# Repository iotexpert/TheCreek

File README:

-----------
creekServer
-----------
jsp that displays the output of the creek database

to build it use 'ant compile' or 'ant'
to deploy it type 'and install'
the username and password is hardcoded in the build file

-------------
creekFirmware
-------------
a zip file of the firmware running on the psoc

----------
getCreek
---------
The program that runs on the rasperry PI.
reads the i2c
figures out what the adc value means
writes the data into the database on the RPI

to build
ant build

to install - (which basically copies the directory into the right place
ant install 

To make the program run on the RPI you need to have 
crontab -l
* * * * * /home/pi/getCreek/printData

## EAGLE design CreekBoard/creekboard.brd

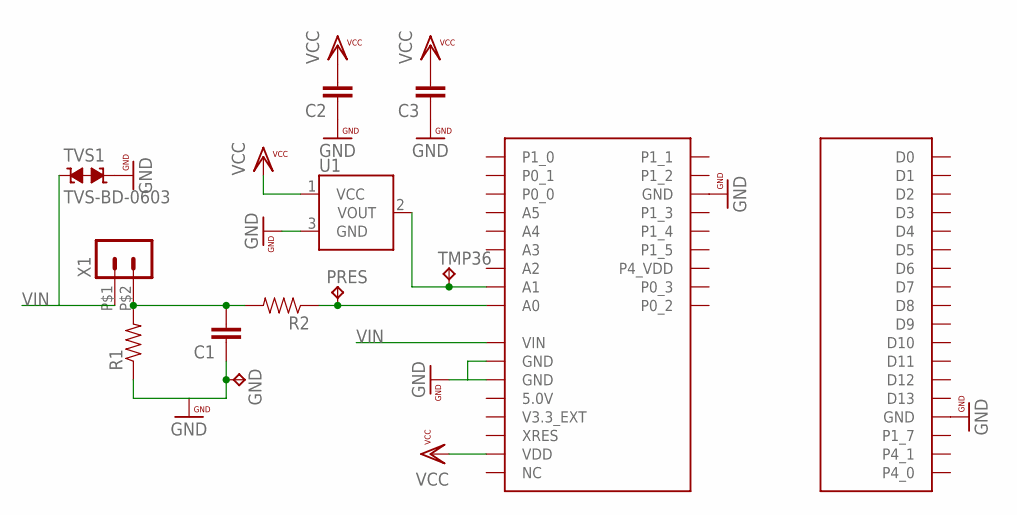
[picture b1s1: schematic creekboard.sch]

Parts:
C1, C2, C3: CAP0603-CAP; 0603-CAP
GND: TP-040
PRES: TP-040
R1: RESISTOR0805-RES; 0805
R2: RESISTOR0603-RES; 0603-RES
TMP36: TP-040
TVS1: TVS-BD-0603; TVS0603
U1: TMP36GT9; TO-92
U2: PIONEERNO_SILK; PIONEER
X1: HEADER_POS2_43650-0200; 43650-0200

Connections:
GND: C1.1, C2.1, C3.1, GND.1, R1.1, TVS1.2, U1.3 (GND), U2.GND@2 (GND), U2.GND@3 (GND), U2.GND@3R (GND), U2.GND@7 (GND)
unnamed: C1.2, R1.2, R2.2, X1.P$2 (2)
unnamed: PRES.1, R2.1, U2.A0
unnamed: TMP36.1, U1.2 (VOUT), U2.A1
VCC: C2.2, C3.2, U1.1 (VCC), U2.P4_VDD1 (VDD)
VIN: TVS1.1, U2.VIN, X1.P$1 (1)

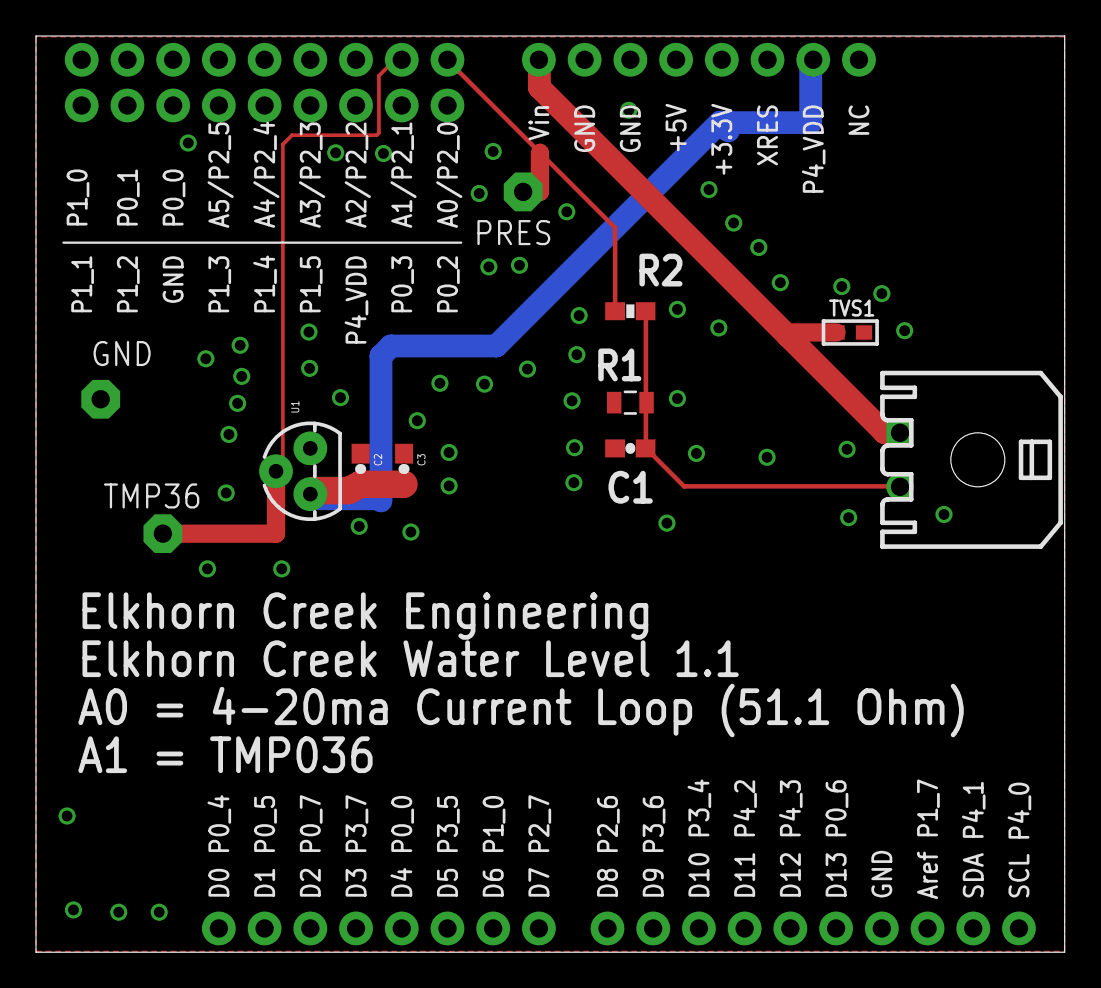
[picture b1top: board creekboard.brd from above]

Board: 2 copper layers, 57.1 x 50.9 mm, 12 parts (0 on the bottom side), 6 nets.

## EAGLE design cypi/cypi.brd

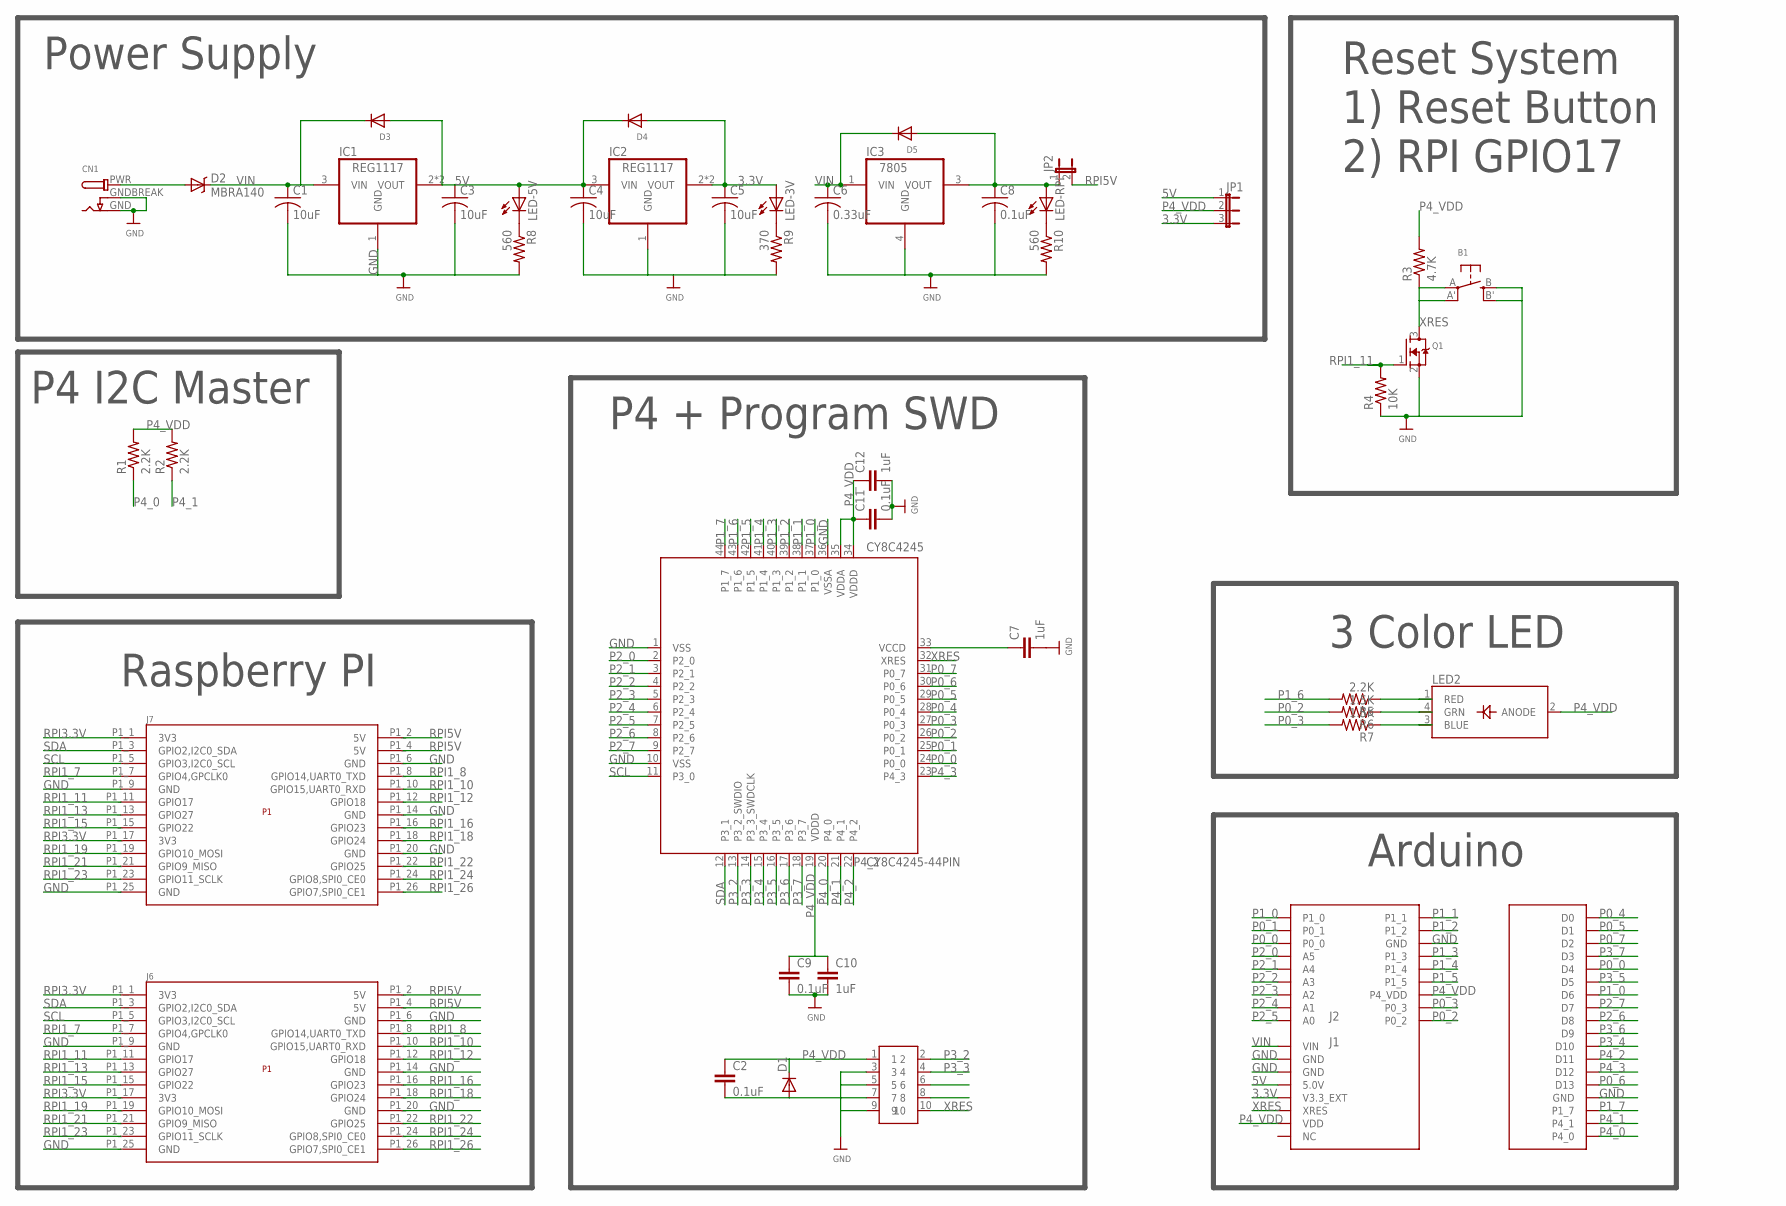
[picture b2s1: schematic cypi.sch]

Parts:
B1: SWITCH_TACT_SMT; EVQ-Q2
C1, C3, C4, C5: 10uF; C0805
C2, C9, C11: 0.1uF; 1206
C6: 0.33uF; C0805
C7, C10, C12: 1uF; 1206
C8: 0.1uF; C0805
CN1: DCBARRELPTH; DCJACK_2MM_PTH
CY8C4245: CY8C4245-44PIN; TQFP-10X10-44
D1: DIODEHV; DIODE-HV
D2: MBRA140; SMA-DIODE
D3, D4, D5: DIODESOD-123; SOD-123
IC1: REG1117; SOT223
IC2: REG1117; SOT223; MPN REG1117
IC3: 7805; DPAK
J5: SAMTEC; FTSH-105-01-XXX-DV-K
J6: RASPBERRY-PI_REV2PINONLY; RPI-PINS
J7: RASPBERRY-PI_REV2
JP1: JP2E; JP2
JP2: JUMPER-2PTH; 1X02
LED2: LED_RGB_PLCC4; RGBLED_PLCC4
LED-3V, LED-5V: LEDCHIPLED_0805; CHIPLED_0805
LED-RPI: LEDCHIPLED_0805; CHIPLED_0805
Q1: MOSFET-NREFLOW; SOT23-R
R1, R2, R5: 2.2K; 0805
R3: 4.7K; 0805
R4: 10K; 0805
R6, R7: 1.5K; 0805
R8, R10: 560; 0805
R9: 370; 0805
U1: PIONEERNO_SILK; PIONEER

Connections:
3.3V: C5.1, D4.A, IC2.2 (VOUT), IC2.4 (VOUT), JP1.3, LED-3V.A, U1.3.3V (V3.3_EXT)
5V: C3.1, C4.1, D3.A, D4.C, IC1.2 (VOUT), IC1.4 (VOUT), IC2.3 (VIN), JP1.1, LED-5V.A, U1.5V (5.0V)
GND: B1.B (S), B1.B' (S1), C1.2, C2.2, C3.2, C4.2, C5.2, C6.2, C7.2, C8.2, C9.2, C10.2, C11.2, C12.2, CN1.GND, CN1.GNDBREAK, CY8C4245.1 (VSS), CY8C4245.10 (VSS), CY8C4245.36 (VSSA), D1.A, IC1.1 (GND), IC2.1 (GND), IC3.4 (GND), J5.3, J5.5, J5.7, J5.9, J6.P1_6 (GND), J6.P1_9 (GND), J6.P1_14 (GND), J6.P1_20 (GND), J6.P1_25 (GND), J7.P1_6 (GND), J7.P1_9 (GND), J7.P1_14 (GND), J7.P1_20 (GND), J7.P1_25 (GND), Q1.2 (S), R4.1, R8.2, R9.2, R10.2, U1.GND@2 (GND), U1.GND@3 (GND), U1.GND@3R (GND), U1.GND@7 (GND)
unnamed: C7.1, CY8C4245.33 (VCCD)
unnamed: C8.1, D5.A, IC3.3 (VOUT), JP2.1, LED-RPI.A
unnamed: CN1.PWR, D2.A
unnamed: LED2.1 (RED), R5.1
unnamed: LED2.4 (GRN), R6.1
unnamed: LED2.3 (BLUE), R7.1
unnamed: LED-5V.C, R8.1
unnamed: LED-3V.C, R9.1
unnamed: LED-RPI.C, R10.1
P0_0: CY8C4245.24 (P0_0), U1.D4, U1.P0_0
P0_1: CY8C4245.25 (P0_1), U1.P0_1
P0_2: CY8C4245.26 (P0_2), R6.2, U1.P0_2
P0_3: CY8C4245.27 (P0_3), R7.2, U1.P0_3
P0_4: CY8C4245.28 (P0_4), U1.D0
P0_5: CY8C4245.29 (P0_5), U1.D1
P0_6: CY8C4245.30 (P0_6), U1.D13
P0_7: CY8C4245.31 (P0_7), U1.D2
P1_0: CY8C4245.37 (P1_0), U1.D6, U1.P1_0
P1_1: CY8C4245.38 (P1_1), U1.P1_1
P1_2: CY8C4245.39 (P1_2), U1.P1_2
P1_3: CY8C4245.40 (P1_3), U1.P1_3
P1_4: CY8C4245.41 (P1_4), U1.P1_4
P1_5: CY8C4245.42 (P1_5), U1.P1_5
P1_6: CY8C4245.43 (P1_6), R5.2
P1_7: CY8C4245.44 (P1_7), U1.AREF (P1_7)
P2_0: CY8C4245.2 (P2_0), U1.A0 (A5)
P2_1: CY8C4245.3 (P2_1), U1.A1 (A4)
P2_2: CY8C4245.4 (P2_2), U1.A2 (A3)
P2_3: CY8C4245.5 (P2_3), U1.A3 (A2)
P2_4: CY8C4245.6 (P2_4), U1.A4 (A1)
P2_5: CY8C4245.7 (P2_5), U1.A5 (A0)
P2_6: CY8C4245.8 (P2_6), U1.D8
P2_7: CY8C4245.9 (P2_7), U1.D7
P3_2: CY8C4245.13 (P3_2_SWDIO), J5.2
P3_3: CY8C4245.14 (P3_3_SWDCLK), J5.4
P3_4: CY8C4245.15 (P3_4), U1.D10
P3_5: CY8C4245.16 (P3_5), U1.D5
P3_6: CY8C4245.17 (P3_6), U1.D9
P3_7: CY8C4245.18 (P3_7), U1.D3
P4_0: CY8C4245.20 (P4_0), R1.1, U1.SCL (P4_0)
P4_1: CY8C4245.21 (P4_1), R2.1, U1.SDA (P4_1)
P4_2: CY8C4245.22 (P4_2), U1.D11
P4_3: CY8C4245.23 (P4_3), U1.D12
P4_VDD: C2.1, C9.1, C10.1, C11.1, C12.1, CY8C4245.19 (VDDD), CY8C4245.34 (VDDD), CY8C4245.35 (VDDA), D1.C, J5.1, JP1.2, LED2.2 (ANODE), R1.2, R2.2, R3.2, U1.P4_VDD, U1.P4_VDD1 (VDD)
RPI1_7: J6.P1_7 (GPIO4,GPCLK0), J7.P1_7 (GPIO4,GPCLK0)
RPI1_8: J6.P1_8 (GPIO14,UART0_TXD), J7.P1_8 (GPIO14,UART0_TXD)
RPI1_10: J6.P1_10 (GPIO15,UART0_RXD), J7.P1_10 (GPIO15,UART0_RXD)
RPI1_11: J6.P1_11 (GPIO17), J7.P1_11 (GPIO17), Q1.1 (G), R4.2
RPI1_12: J6.P1_12 (GPIO18), J7.P1_12 (GPIO18)
RPI1_13: J6.P1_13 (GPIO27), J7.P1_13 (GPIO27)
RPI1_15: J6.P1_15 (GPIO22), J7.P1_15 (GPIO22)
RPI1_16: J6.P1_16 (GPIO23), J7.P1_16 (GPIO23)
RPI1_18: J6.P1_18 (GPIO24), J7.P1_18 (GPIO24)
RPI1_19: J6.P1_19 (GPIO10_MOSI), J7.P1_19 (GPIO10_MOSI)
RPI1_21: J6.P1_21 (GPIO9_MISO), J7.P1_21 (GPIO9_MISO)
RPI1_22: J6.P1_22 (GPIO25), J7.P1_22 (GPIO25)
RPI1_23: J6.P1_23 (GPIO11_SCLK), J7.P1_23 (GPIO11_SCLK)
RPI1_24: J6.P1_24 (GPIO8,SPI0_CE0), J7.P1_24 (GPIO8,SPI0_CE0)
RPI1_26: J6.P1_26 (GPIO7,SPI0_CE1), J7.P1_26 (GPIO7,SPI0_CE1)
RPI3.3V: J6.P1_1 (3V3), J6.P1_17 (3V3), J7.P1_1 (3V3), J7.P1_17 (3V3)
RPI5V: J6.P1_2 (5V), J6.P1_4 (5V), J7.P1_2 (5V), J7.P1_4 (5V), JP2.2
SCL: CY8C4245.11 (P3_0), J6.P1_5 (GPIO3,I2C0_SCL), J7.P1_5 (GPIO3,I2C0_SCL)
SDA: CY8C4245.12 (P3_1), J6.P1_3 (GPIO2,I2C0_SDA), J7.P1_3 (GPIO2,I2C0_SDA)
VIN: C1.1, C6.1, D2.C, D3.C, D5.C, IC1.3 (VIN), IC3.1 (VIN), U1.VIN
XRES: B1.A, B1.A' (P1), CY8C4245.32 (XRES), J5.10, Q1.3 (D), R3.1, U1.XRES

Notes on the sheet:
Power Supply
Reset System 1) Reset Button 2) RPI GPIO17
P4 I2C Master
P4 + Program SWD
Raspberry PI
Arduino
3 Color LED

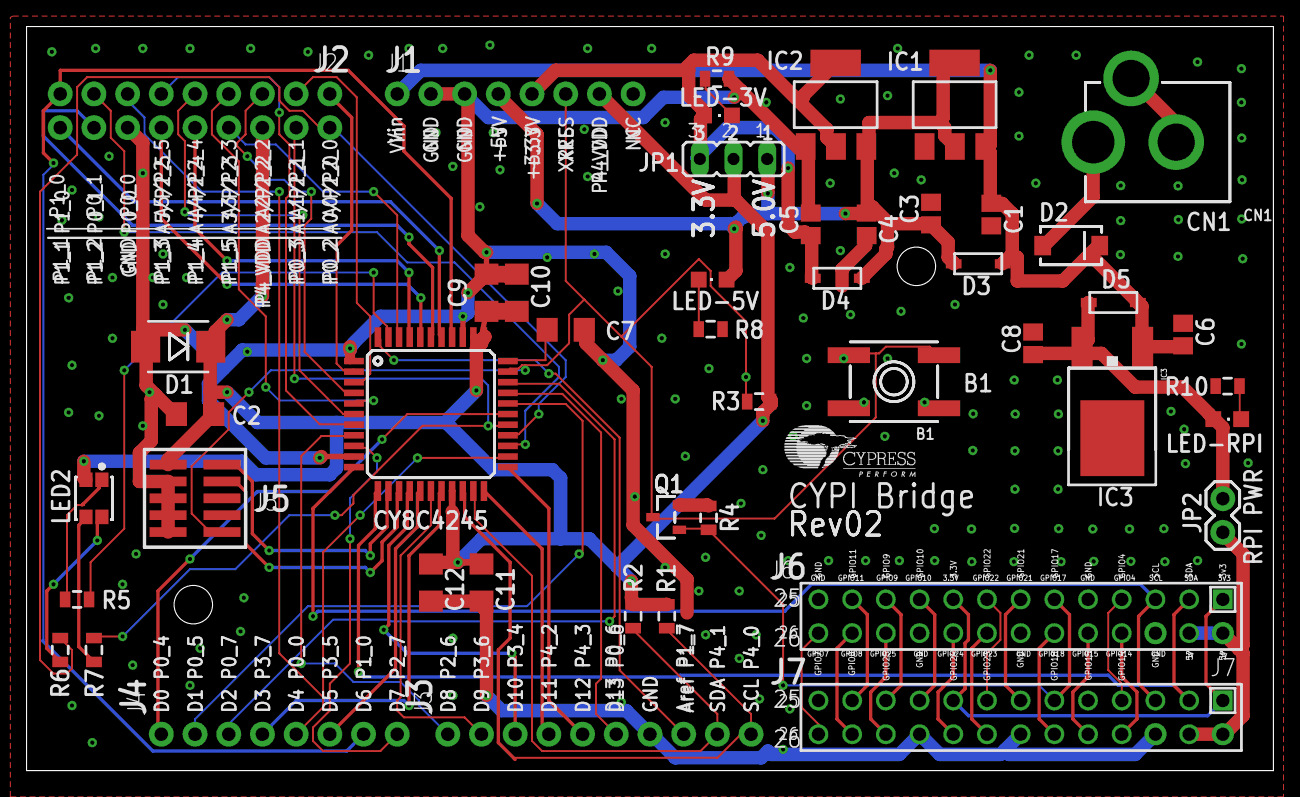
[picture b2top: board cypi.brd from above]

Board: 2 copper layers, 94.0 x 56.1 mm, 44 parts (0 on the bottom side), 68 nets.

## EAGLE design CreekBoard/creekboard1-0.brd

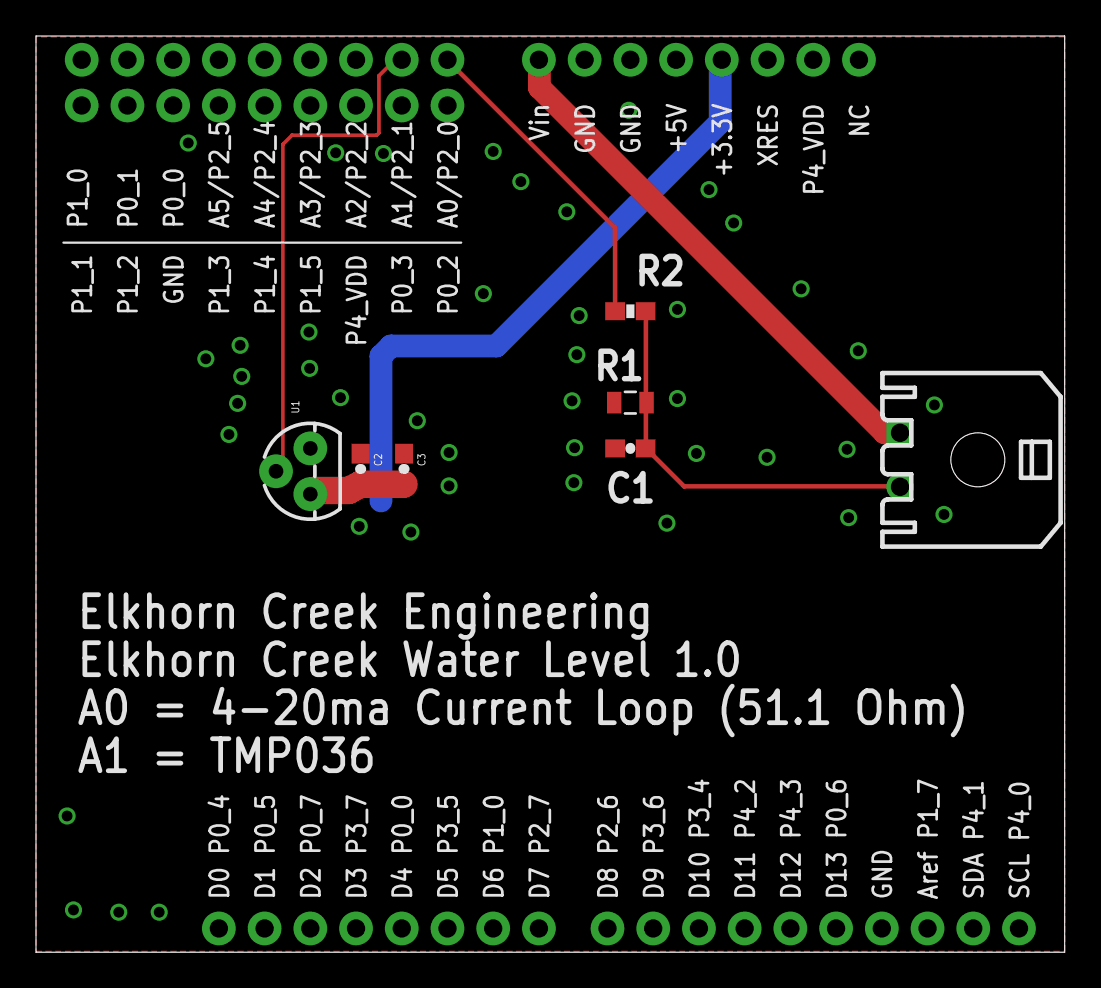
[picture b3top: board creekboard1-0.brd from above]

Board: 2 copper layers, 57.1 x 50.9 mm, 8 parts (0 on the bottom side), 6 nets.

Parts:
C1, C2, C3: 0603-CAP
R1: 0805
R2: 0603-RES
U1: TO-92
U2: PIONEERNO_SILK; PIONEER
X1: 43650-0200

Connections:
GND: C1.1, C2.1, C3.1, R1.1, U1.3, U2.GND@2, U2.GND@3, U2.GND@3R, U2.GND@7
unnamed: C1.2, R1.2, R2.2, X1.P$2
unnamed: R2.1, U2.A0
unnamed: U1.2, U2.A1
VCC: C2.2, C3.2, U1.1, U2.3.3V
VIN: U2.VIN, X1.P$1

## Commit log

2012-12-28 Initial
2012-12-28 added files
2012-12-28 added a bunch of files
2013-01-13 cleaning up the project
2013-03-24 added README
2013-03-24 updated some stuff
2013-03-24 removed fu getCreek
2013-03-24 fixed getCreek
2013-03-24 updated build for install
2013-03-24 fixed up the build file to make the ant task scp work... and updated the readme
2013-03-30 Moved the project into eclipse. Modified the I2c to enable reading both the adc and the filter values
2013-03-30 Updated default target
2013-03-31 fixed bug in process not ending
2013-03-31 added another chart + added ant build to eclipse configuration
2013-03-31 made the chart read from the filtered value in the database
2013-05-12 fixed up problems with the retrieving data from the psoc
2013-05-12 automated chart creation
2013-06-02 added i2cdb and new interface ... much better
2013-06-02 updated chart
2013-10-12 re did server
2013-10-12 changed config for p5lp
2013-10-13 excel export
2013-10-13 Fixed everything up + cleaned up jsps
2013-10-13 Cleanup
2013-10-13 changed range of plot
2013-11-02 Changed columns
2013-11-02 fixed up temperature
2015-08-23 added rpi side
2015-08-23 done
2015-08-31 asdf
2016-01-30 checked some changes for some unknown reason
2016-01-30 Added 1.0 board as seperate files
2016-01-31 re-organized files
2016-01-31 Fixed readme.md
2016-01-31 Took CYPI out of repository
2016-02-07 removed all bad firmware junk
2016-02-07 Fixed Creek Firmware
2016-02-08 A few cleanups of the project
2016-04-09 Fixed up getCreek
2016-04-15 Fixed up getCreek Java Programs
2016-04-17 First checkin of massive changes to Java server
2016-04-18 Updates for creekserver 1.1
2016-04-24 added program TestData which can insert test data into database
2016-04-30 preparing for jsp
2016-05-02 updates for 1.2
2016-05-02 bunches of updates for 1.2
2016-05-04 Updated model object for MVC
2016-05-04 formatting updates
2016-05-08 A bunch of updates for Creek Server 1.2
2016-05-08 Fixed signficant digits on flood events table
2017-06-24 Updated with table
2020-05-25 Updated the creekfirmware for new algorithm for depth calculation
2020-05-25 Update the history to show correct table of markers
2020-05-25 added powerpoint diagram
2020-05-25 added cypi-bootloader
2020-05-25 updated ignore file
2020-05-25 Updated the readme
2020-05-25 updated configproperties

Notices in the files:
parts and their libraries:
SparkFun-Passives: Licensing: Creative Commons ShareAlike 4.0 International - https://creativecommons.org/licenses/by-sa/4.0
supressor: Copyright (C) 2009, Bob Starr
PatternAgents-Beautify: License : http://creativecommons.org/licenses/by-sa/3.0
(Creative Commons 3.0)
